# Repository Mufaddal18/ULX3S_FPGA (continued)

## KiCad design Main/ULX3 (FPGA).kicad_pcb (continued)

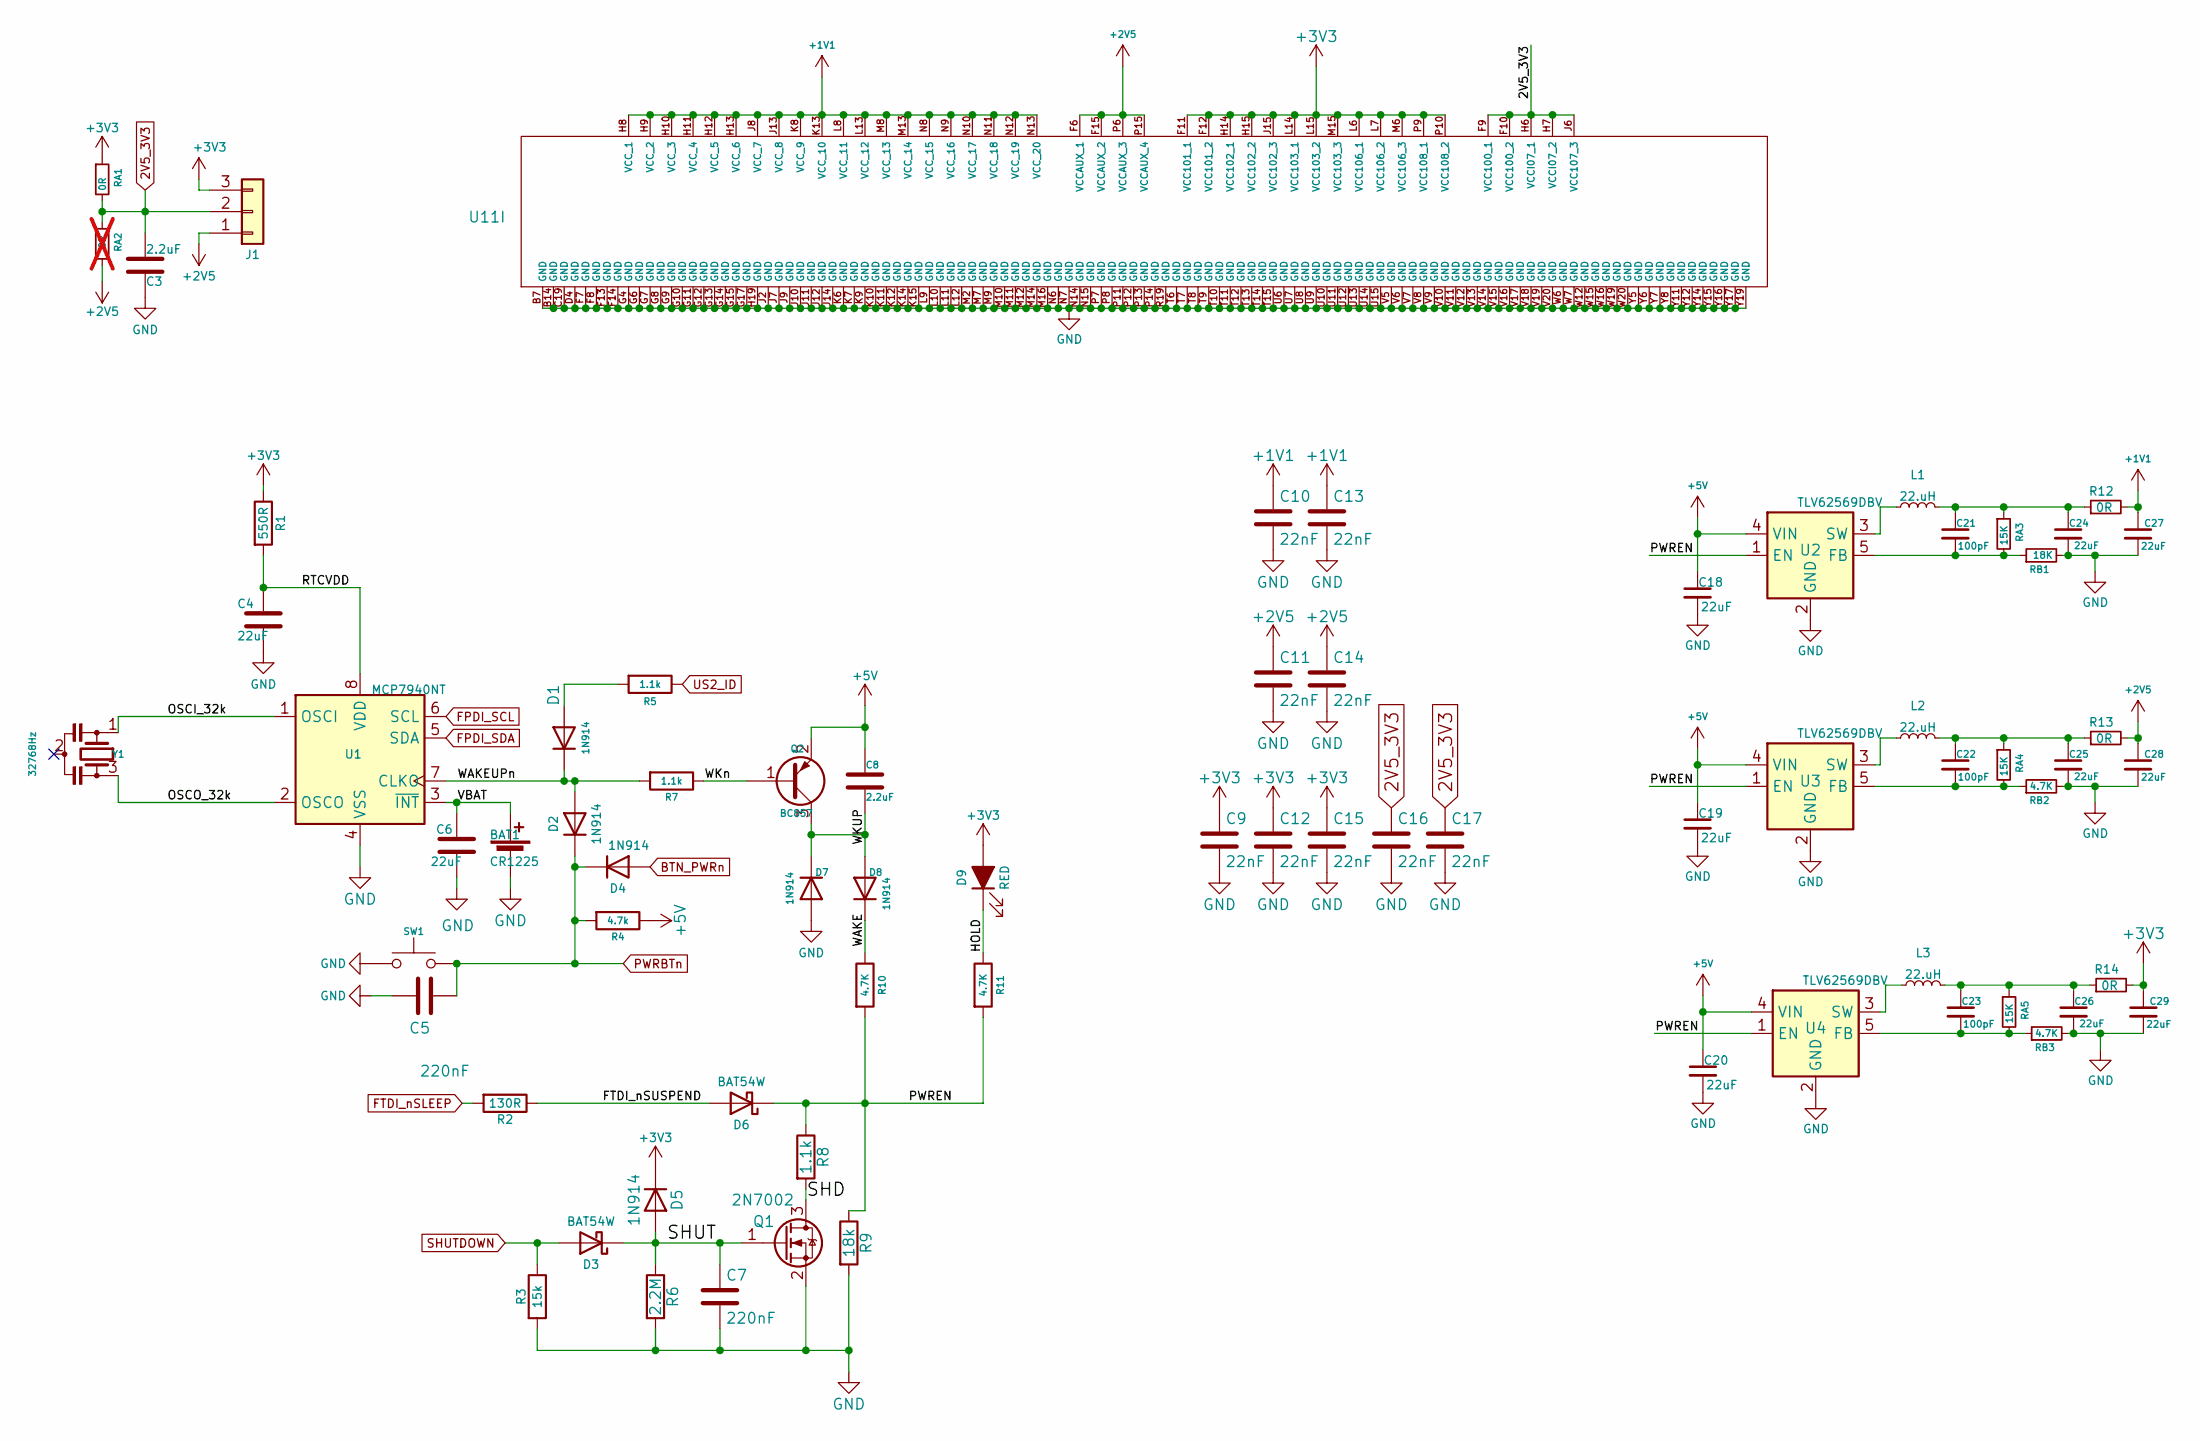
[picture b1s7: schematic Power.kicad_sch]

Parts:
BAT1: CR1225; Keystone_3000_1x12mm-CoinCell; MPN 3000TR; Mouser 614-SMTM1225.TR
C3: 2.2uF; C_0402_1005Metric; MPN CC0805MRX5R6BB225
C4: 22uF; C_0603_1608Metric; MPN CC0805ZKY5V5BB226
C5: 220nF; C_0402_1005Metric
C6: 22uF; C_0805_2012Metric; MPN CC0805ZKY5V5BB226
C7: 220nF; C_0402_1005Metric; MPN CC0603KRX7R8BB224; Mouser 603-CC603KRX7R6BB224
C8: 2.2uF; C_0805_2012Metric; MPN CC0805MRX5R6BB225; Mouser 187-CL21B225KOFNNNG
C9: 22nF; C_0603_1608Metric; MPN CC0603JRX7R8BB223; Mouser 603-CC603KRX7R7BB223
C10, C11, C12, C13, C14, C15, C16, C17: 22nF; C_0603_1608Metric; MPN CX0603MRX7R8BB223
C18, C19, C20, C24, C25, C26, C27, C28, C29: 22uF; C_0402_1005Metric
C21, C22, C23: 100pF; C_0603_1608Metric
D1, D4, D5, D7, D8: 1N914; D_SOD-323_HandSoldering
D2: 1N914; D_SOD-323_HandSoldering; MPN 1N4148WS; Mouser 241-1N4148WSR100001
D3: BAT54W; D_SOD-323_HandSoldering; MPN NSR0530HT1G; Mouser 771-BAT54J115
D6: BAT54W; D_SOD-323_HandSoldering
D9: RED; LED_0402_1005Metric
J1: PinHeader_1x03_P2.54mm_Vertical
L1, L2, L3: 22.uH; L_0402_1005Metric
Q1: 2N7002; SOT-23; MPN 2N7002P,215; Mouser 512-2N7002L
Q2: BC857; SOT-23; MPN BC857; Mouser 583-BC856A-T
R1: 550R; R_0402_1005Metric
R2: 130R; R_0402_1005Metric
R3: 15k; R_0402_1005Metric
R4: 4.7k; R_0402_1005Metric; MPN AC0603FR-104K7L
R5, R7, R8: 1.1k; R_0402_1005Metric
R6: 2.2M; R_0402_1005Metric; MPN RC0603FR-132M2L; Mouser 603-AC0603FR-072M2L
R9: 18k; R_0402_1005Metric
R10: 4.7K; R_0402_1005Metric; MPN AC0603FR-104K7L; Mouser 755-SFR03EZPF4701
R11: 4.7K; R_0402_1005Metric; MPN AC0603FR-104K7L
R12, R13, R14: 0R; R_0402_1005Metric
RA1: 0R; R_0402_1005Metric
RA2: 0R; R_0402_1005Metric; not fitted
RA3, RA4, RA5: 15K; R_0402_1005Metric
RB1: 18K; R_0402_1005Metric
RB2, RB3: 4.7K; R_0402_1005Metric
SW1: PTS810SJG250SMTRLFS
U1: MCP7940NT; MCP794NT; MPN MCP7940NT-I/SN; Mouser 579-MCP7940NT-I/SN
U2, U3, U4: TLV62569DBV; SOT-23-5
U11: Latice_LEF5U_FPGA_BGA-381
Y1: 32768Hz; Resonator_Q13FC

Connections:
2V5_3V3: C3.1, C16.1, C17.1, J1.2, RA1.2, RA2.1, U11.F9 (VCC100_1), U11.F10 (VCC100_2), U11.H6 (VCCI07_1), U11.H7 (VCCI07_2), U11.J6 (VCC107_3); also elsewhere on the board
+1V1: C10.1, C13.1, C27.1, R12.2, U11.H8 (VCC_1), U11.H9 (VCC_2), U11.H10 (VCC_3), U11.H11 (VCC_4), U11.H12 (VCC_5), U11.H13 (VCC_6), U11.J8 (VCC_7), U11.J13 (VCC_8), U11.K8 (VCC_9), U11.K13 (VCC_10), U11.L8 (VCC_11), U11.L13 (VCC_12), U11.M8 (VCC_13), U11.M13 (VCC_14), U11.N8 (VCC_15), U11.N9 (VCC_16), U11.N10 (VCC_17), U11.N11 (VCC_18), U11.N12 (VCC_19), U11.N13 (VCC_20)
+2V5: C11.1, C14.1, C28.1, J1.1, R13.2, RA2.2, U11.F6 (VCCAUX_1), U11.F15 (VCCAUX_2), U11.P6 (VCCAUX_3), U11.P15 (VCCAUX_4); also elsewhere on the board
+3V3: C9.1, C12.1, C15.1, C29.1, D5.1 (K), D9.2 (A), J1.3, R1.1, R14.2, RA1.1, U11.F11 (VCC101_1), U11.F12 (VCC101_2), U11.H14 (VCC102_1), U11.H15 (VCC102_2), U11.J15 (VCC102_3), U11.L6 (VCC106_1), U11.L7 (VCC106_2), U11.L14 (VCC103_1), U11.L15 (VCC103_2), U11.M6 (VCC106_3), U11.M15 (VCC103_3), U11.P9 (VCC108_1), U11.P10 (VCC108_2); also elsewhere on the board
+5V: C8.1, C18.1, C19.1, C20.1, Q2.2 (E), R4.1, U2.4 (VIN), U3.4 (VIN), U4.4 (VIN); also elsewhere on the board
/Power/FTDI_nSUSPEND: D6.2 (A), R2.1
/Power/HOLD: D9.1 (K), R11.1
/Power/OSCI_32k: U1.1 (OSCI), Y1.1
/Power/OSCO_32k: U1.2 (OSCO), Y1.3
/Power/PWREN: D6.1 (K), R8.1, R9.1, R10.2, R11.2, U2.1 (EN), U3.1 (EN), U4.1 (EN)
/Power/RTCVDD: C4.1, R1.2, U1.8 (VDD)
/Power/SHD: Q1.3 (D), R8.2
/Power/SHUT: C7.1, D3.1 (K), D5.2 (A), Q1.1 (G), R6.1
/Power/VBAT: C6.1, U1.3 (~INT)
/Power/WAKE: D8.1 (K), R10.1
/Power/WAKEUPn: D1.1 (K), D2.2 (A), R7.2, U1.7 (CLKO)
/Power/WKUP: C8.2, D7.1 (K), D8.2 (A), Q2.3 (C)
/Power/WKn: Q2.1 (B), R7.1
BTN_PWRn: D4.2 (A); also elsewhere on the board
FPDI_SCL: U1.6 (SCL); also elsewhere on the board
FPDI_SDA: U1.5 (SDA); also elsewhere on the board
FTDI_nSLEEP: R2.2; also elsewhere on the board
unnamed: C21.1, C24.1, L1.2, R12.1, RA3.1
unnamed: C22.1, C25.1, L2.2, R13.1, RA4.1
unnamed: C23.1, C26.1, L3.2, R14.1, RA5.1
unnamed: D1.2 (A), R5.2
unnamed: C21.2, RA3.2, RB1.1, U2.5 (FB)
unnamed: L1.1, U2.3 (SW)
unnamed: C22.2, RA4.2, RB2.1, U3.5 (FB)
unnamed: L2.1, U3.3 (SW)
unnamed: C23.2, RA5.2, RB3.1, U4.5 (FB)
unnamed: L3.1, U4.3 (SW)
SHUTDOWN: D3.2 (A), R3.1
US2_ID: R5.1

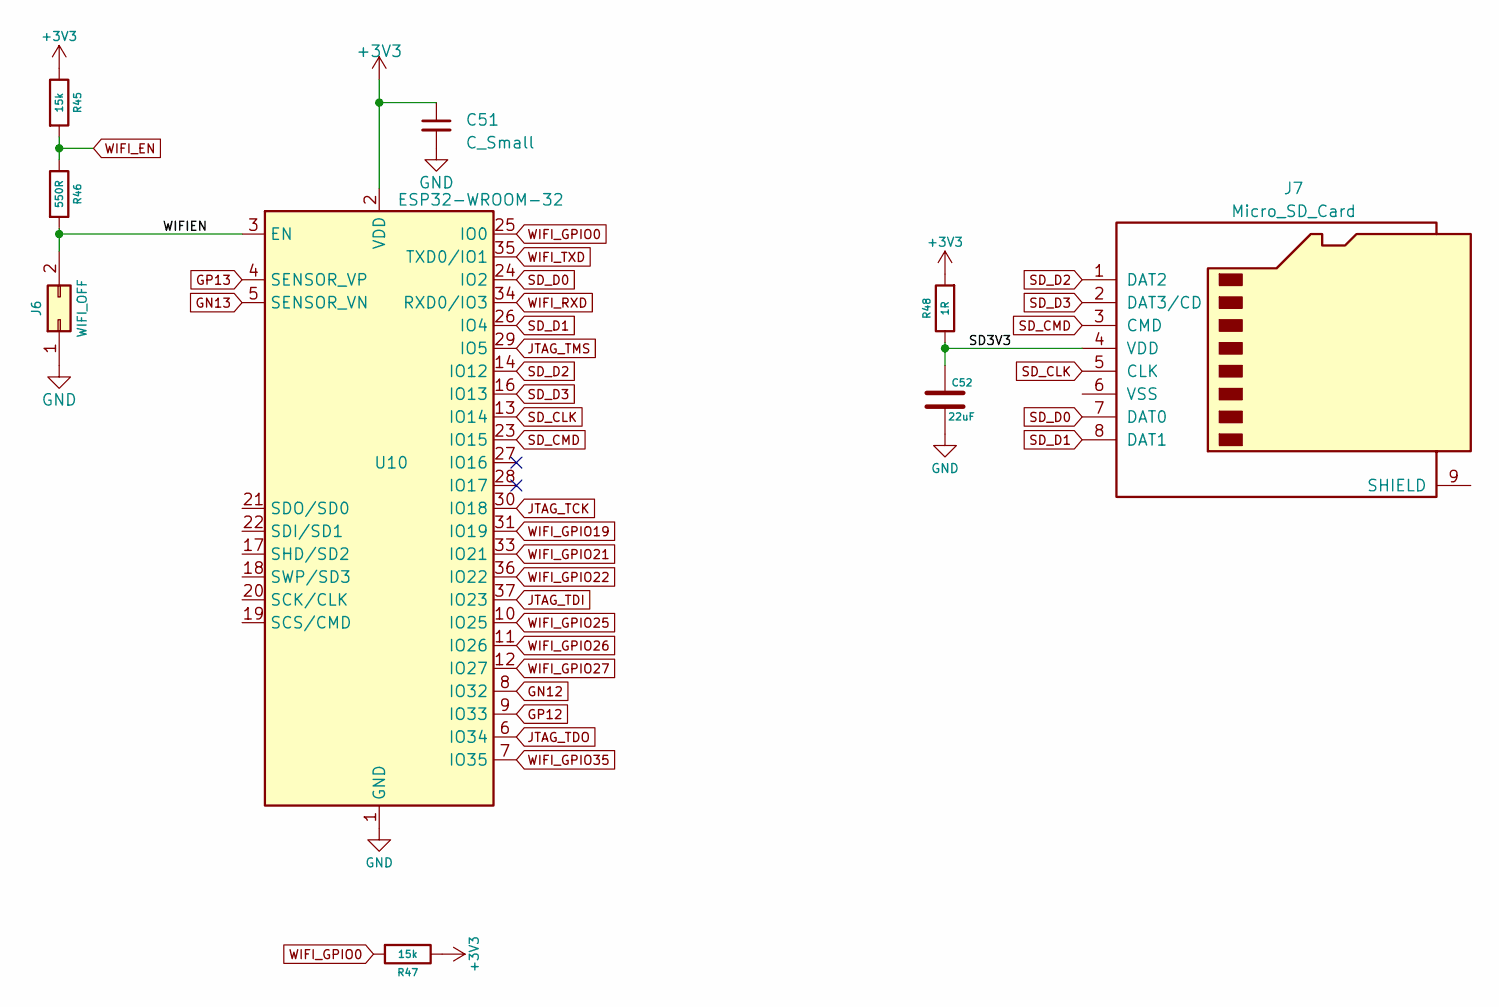
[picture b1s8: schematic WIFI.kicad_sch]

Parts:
C51: C_Small; C_0603_1608Metric
C52: 22uF; C_0805_2012Metric; MPN CC0805ZKY5V5BB226
J6: WIFI_OFF; PinHeader_1x02_P2.54mm_Vertical
J7: Micro_SD_Card; 1040310811
R45, R47: 15k; R_0402_1005Metric
R46: 550R; R_0402_1005Metric
R48: 1R; R_0402_1005Metric; MPN 73L2R47J; Mouser 774-73L2R47J
U10: ESP32-WROOM-32

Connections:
+3V3: C51.1, R45.1, R47.1, R48.2, U10.2 (VDD); also elsewhere on the board
/WIFI/SD3V3: C52.1, J7.4 (VDD), R48.1
/WIFI/WIFIEN: J6.2, R46.2, U10.3 (EN)
GN12: U10.8 (IO32); also elsewhere on the board
GN13: U10.5 (SENSOR_VN); also elsewhere on the board
GP12: U10.9 (IO33); also elsewhere on the board
GP13: U10.4 (SENSOR_VP); also elsewhere on the board
JTAG_TCK: U10.30 (IO18); also elsewhere on the board
JTAG_TDI: U10.37 (IO23); also elsewhere on the board
JTAG_TDO: U10.6 (IO34); also elsewhere on the board
JTAG_TMS: U10.29 (IO5); also elsewhere on the board
SD_CLK: J7.5 (CLK), U10.13 (IO14); also elsewhere on the board
SD_CMD: J7.3 (CMD), U10.23 (IO15); also elsewhere on the board
SD_D0: J7.7 (DAT0), U10.24 (IO2); also elsewhere on the board
SD_D1: J7.8 (DAT1), U10.26 (IO4); also elsewhere on the board
SD_D2: J7.1 (DAT2), U10.14 (IO12); also elsewhere on the board
SD_D3: J7.2 (DAT3/CD), U10.16 (IO13); also elsewhere on the board
WIFI_EN: R45.2, R46.1; also elsewhere on the board
WIFI_GPIO0: R47.2, U10.25 (IO0); also elsewhere on the board
WIFI_GPIO19: U10.31 (IO19); also elsewhere on the board
WIFI_GPIO21: U10.33 (IO21); also elsewhere on the board
WIFI_GPIO22: U10.36 (IO22); also elsewhere on the board
WIFI_GPIO25: U10.10 (IO25); also elsewhere on the board
WIFI_GPIO26: U10.11 (IO26); also elsewhere on the board
WIFI_GPIO27: U10.12 (IO27); also elsewhere on the board
WIFI_GPIO35: U10.7 (IO35); also elsewhere on the board
WIFI_RXD: U10.34 (RXD0/IO3); also elsewhere on the board
WIFI_TXD: U10.35 (TXD0/IO1); also elsewhere on the board

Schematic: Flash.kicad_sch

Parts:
D10: 1N914; D_SOD-523
D11: IN914; D_SOD-523
R15, R16, R17, R18: 10K; R_0402_1005Metric
R19: 1K; R_0402_1005Metric
R20: 4.7K; R_0402_1005Metric
R21, R22, R23: 15K; R_0402_1005Metric
U7: IS25LP128F-JBLE; Flash_IS25LP128F
U11: Latice_LEF5U_FPGA_BGA-381

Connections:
+3V3: R15.1, R16.1, R17.1, R18.1, R19.1, R20.1, R21.1, R22.1, R23.1, U7.8 (VCC), U11.T2 (SN/CSn), U11.T3 (WRITEn), U11.T4 (CFG_1), U11.U2 (CS1n); also elsewhere on the board
/Flash/FLASH_DONE: U11.Y3 (DONE)
/Flash/FLASH_INITN: U11.V3 (INITn)
/Flash/FLASH_MISO: R17.2, U7.2 (MISO), U11.V2 (D1/MISO)
/Flash/FLASH_MOSI: R18.2, U7.5 (MOSI), U11.W2 (D0/MOSI)
/Flash/FLASH_PROGRAMN: U11.W3 (PROGRAMn)
/Flash/FLASH_SCK: R19.2, U7.6 (SCK), U11.U3 (CCLK)
/Flash/FLASH_nCS: R20.2, U7.1 (~CS), U11.R2 (CSSPIN)
/Flash/FLASH_nHOLD: R16.2, U7.7 (~HOLD), U11.W1 (D3/HOLDn)
/Flash/FLASH_nWP: R15.2, U7.3 (~WP), U11.Y2 (D2/WPn)
/Flash/FPGA_DONE: R22.2
/Flash/FPGA_INITN: R23.2
/Flash/FPGA_PROGRAMN: D10.2 (A), D11.2 (A), R21.2
BTN_D: U11.V1 (D4/MOSI2); also elsewhere on the board
BTN_F2: U11.T1 (D6); also elsewhere on the board
BTN_L: U11.U1 (D5/MISO2); also elsewhere on the board
USER_PROGRAMN: D11.1 (K); also elsewhere on the board

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
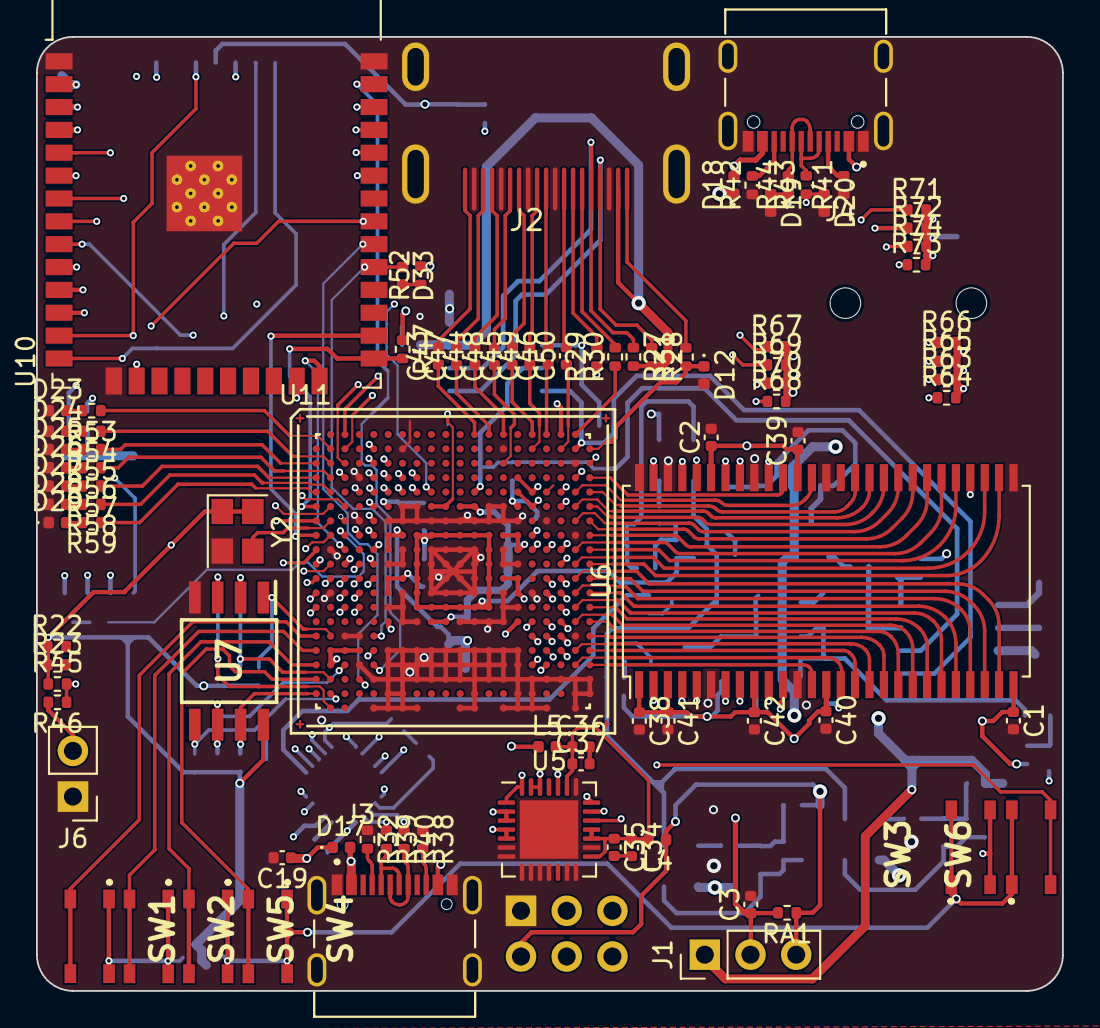
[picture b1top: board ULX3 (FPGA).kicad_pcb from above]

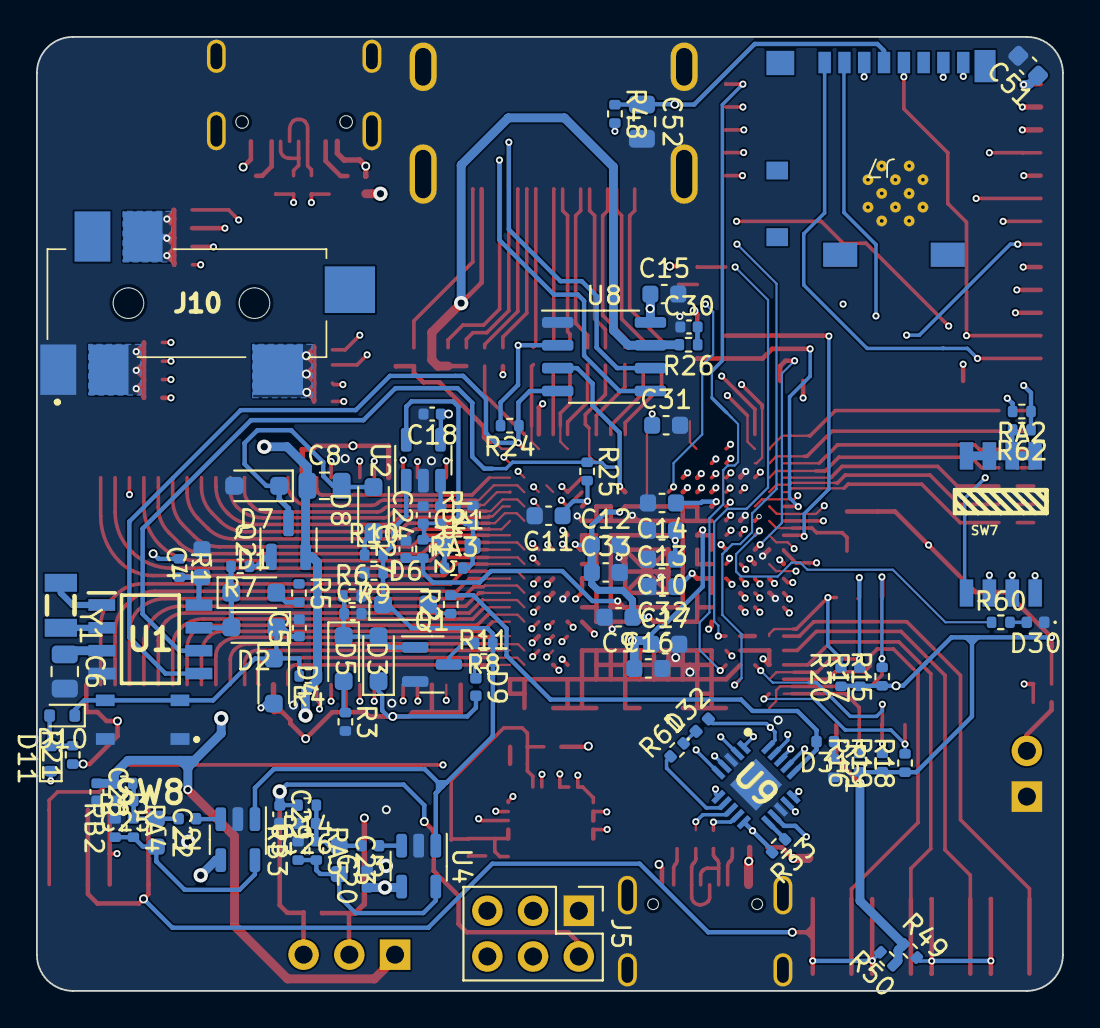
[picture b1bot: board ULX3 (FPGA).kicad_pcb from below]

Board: 8 copper layers, 57.0 x 53.0 mm, 193 parts (101 on the bottom side), 216 nets.

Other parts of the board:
C31, C32, C33: 22nF; C_0603_1608Metric
SW8: PTS810SJG250SMTRLFS

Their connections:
2V5_3V3: C31.1; also elsewhere on the board
+3V3: C32.1, C33.1; also elsewhere on the board
